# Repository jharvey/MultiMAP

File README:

This is a circuit board that would most typically be used for automotive engines running ITB setups. This board will combine multiple MAP signals, and report the lowest MAP signal to the engine control computer. This project includes designs for 2,4,6,8 and 12 MAP signals. 

This project includes, Gerber MFG files that can be uploaded to almost any MFG house, such that PCB's can be obtained. It includes BOM's and simulation files, as well as the KICAD PCB layout files. 

I have also uploaded files to BatchPCB, such that if someone want's the board, they can simply go there and purchase it.

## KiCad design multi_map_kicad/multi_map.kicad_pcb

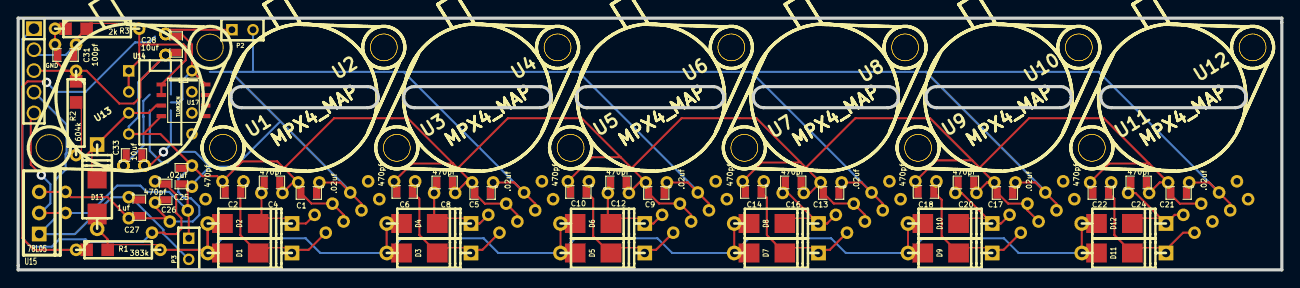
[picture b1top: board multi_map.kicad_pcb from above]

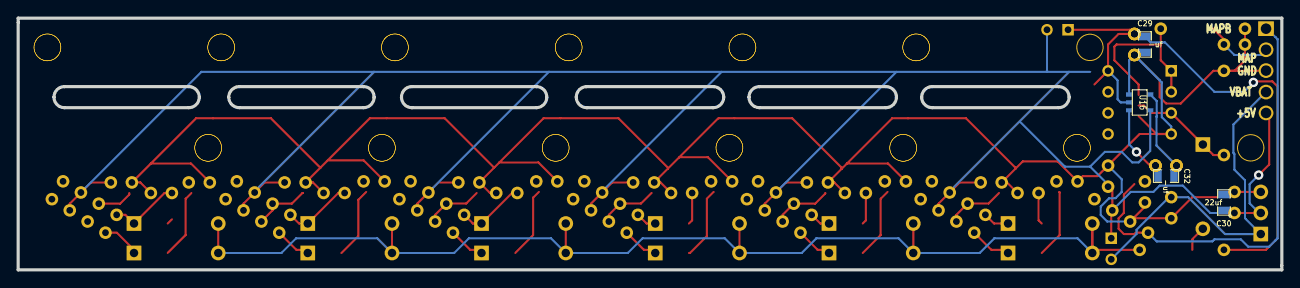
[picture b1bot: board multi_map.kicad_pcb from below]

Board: 2 copper layers, 152.4 x 30.4 mm, 63 parts (4 on the bottom side), 22 nets.

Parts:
C1, C5, C9, C13, C17, C21, C25: .02uf; SM0805-C1
C2, C4, C6, C8, C10, C12, C14, C16, C18, C20, C22, C24, C26: 470pf; SM0805-C1
C27: 1uf; SM0805-C1
C28, C33: 10uf; SM0805-C1
C29, C32: -uf; SM0805-C1
C30: 22uf; SM0805-C1
C31: 100pf; SM0805-C1
D1, D2, D3, D4, D5, D6, D7, D8, D9, D10, D11, D12, D13: DIODE; D4-SMB
P1: CONN_5; SIL-5
P2, P3: CONN_2; SIL-2
R1: 383k; R4-SM0805
R2: 604k; R4-SM0805
R3: 2k; R4-SM0805
U1, U3, U5, U7, U9, U11, U13: MPX4_MAP; MPX-4_MAP_2
U2, U4, U6, U8, U10, U12: MPX4_MAP; MPX-4_MAP
U14: TL082CN; 8dip300
U15: 78L05; TO220_VERT
U16: MAX1682; SOT23-5
U17: TL082CN; SO8E

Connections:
+5v_1: C1.1, C5.1, C9.1, C13.1, C17.1, C21.1, C25.1, C30.1, P1.5, P2.2, P3.1, U1.3, U2.3, U3.3, U4.3, U5.3, U6.3, U7.3, U8.3, U9.3, U10.3, U11.3, U12.3, U13.3, U15.3, U16.4
+10v_1: C28.1, C29.1, P2.1, R1.1, U14.8, U16.2, U17.8
GND: C1.2, C2.2, C4.2, C5.2, C6.2, C8.2, C9.2, C10.2, C12.2, C13.2, C14.2, C16.2, C17.2, C18.2, C20.2, C21.2, C22.2, C24.2, C25.2, C26.2, C27.2, C28.2, C29.2, C30.2, C31.2, P1.3, R2.1, R3.1, U1.2, U2.2, U3.2, U4.2, U5.2, U6.2, U7.2, U8.2, U9.2, U10.2, U11.2, U12.2, U13.2, U14.4, U15.2, U16.1, U17.4
MAP1_1: C2.1, D1.2, U1.1
MAP2_1: C4.1, D2.2, U2.1
MAP3_1: C6.1, D3.2, U3.1
MAP4_1: C8.1, D4.2, U4.1
MAP5_1: C10.1, D5.2, U5.1
MAP6_1: C12.1, D6.2, U6.1
MAP7_1: C14.1, D7.2, U7.1
MAP8_1: C16.1, D8.2, U8.1
MAP9_1: C18.1, D9.2, U9.1
MAP10_1: C20.1, D10.2, U10.1
MAP11_1: C22.1, D11.2, U11.1
MAP12_1: C24.1, D12.2, U12.1
MAPB_1: C26.1, P1.1, U13.1
unnamed: C32.1, C33.1, U16.5
unnamed: C32.2, C33.2, U16.3
unnamed: D1.1, D2.1, D3.1, D4.1, D5.1, D6.1, D7.1, D8.1, D9.1, D10.1, D11.1, D12.1, D13.1, R1.2
OP+_1: D13.2, R2.2, U14.3, U17.3
OP-_1: C31.1, P1.2, R3.2, U14.1, U14.2, U17.1, U17.2
VBAT_1: C27.1, P1.4, P3.2, U15.1

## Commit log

2011-03-27 moved to git hub from google code
2011-10-16 Moved pictures around in their folders, changed license to MIT.
2011-10-16 Added README per git hub suggestion.
2011-10-17 Change to internal markdown format. Can't rename on the server, so will do that locally next.
2011-10-17 Migrate to markdown extension.
2020-05-19 Updated to KC4
2020-05-19 Updated to KC5
